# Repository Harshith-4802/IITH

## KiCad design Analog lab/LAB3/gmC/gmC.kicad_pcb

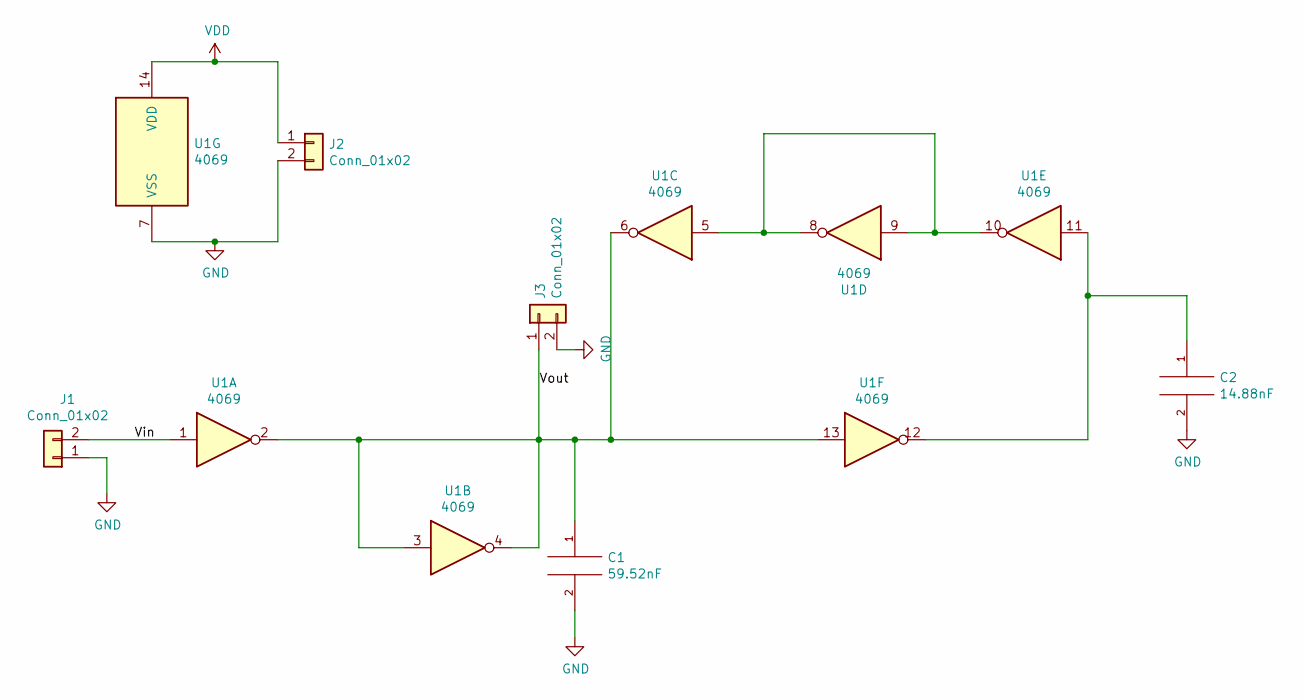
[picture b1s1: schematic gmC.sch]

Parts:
C1: 59.52nF; C_Disc_D3.0mm_W1.6mm_P2.50mm
C2: 14.88nF; C_Disc_D3.0mm_W1.6mm_P2.50mm
J1, J2, J3: Conn_01x02; Banana_Jack_2Pin
U1: 4069; DIP-14_W7.62mm

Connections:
/Vin: J1.2, U1.1
/Vout: C1.1, J3.1, U1.2, U1.3, U1.4, U1.6, U1.13
GND: C1.2, C2.2, J1.1, J2.2, J3.2, U1.7 (VSS)
unnamed: C2.1, U1.11, U1.12
unnamed: U1.5, U1.8, U1.9, U1.10
VDD: J2.1, U1.14 (VDD)

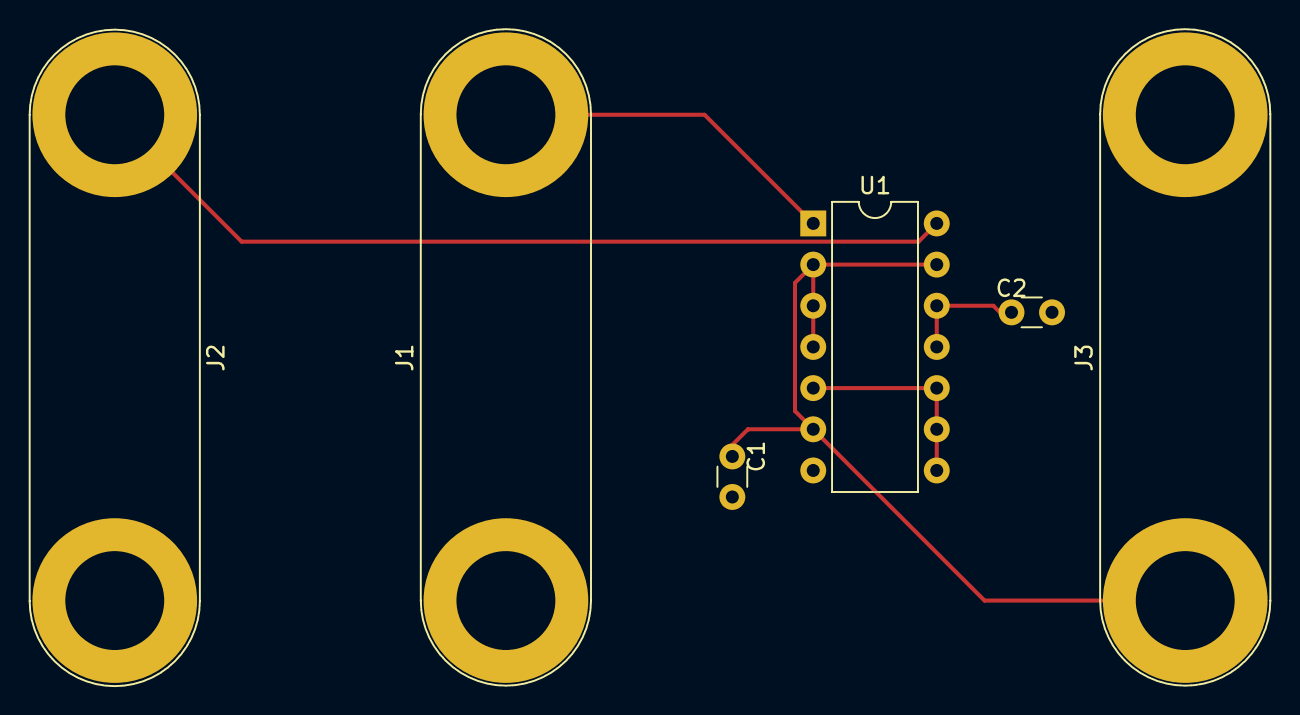
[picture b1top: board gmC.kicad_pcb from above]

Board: 2 copper layers, 6 parts (0 on the bottom side), 6 nets.

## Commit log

2022-08-23 adding files
2022-09-01 Lab 2
